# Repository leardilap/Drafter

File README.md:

# drafter

# Idea
- any usb keyboard -> transparent forward to PC as well
- [e-ink screen x3](https://www.exp-tech.de/displays/e-paper-e-ink/8887/waveshare-2.9-e-ink-raw-display-panel-three-color-296x128?c=1424)
- tinyFPGA-EX
- [ER-TFT0784-1 IPS TFT IoT LCD Display 1280x400 MIPI](https://www.buydisplay.com/7-84-inch-bar-style-ips-tft-iot-lcd-display-1280x400-mipi-for-car-monitor)
- [contition circuits to make the screen work](https://www.adafruit.com/product/4224)
- 3d printed case
- uSD card to save files -> in tinyFPGA-EX already, should be visible from the PC to copy and edit the files later on
- Firmware to print basic menu in screen and decode the keys and print in screen -> try to find a keyboard FPGA code already
- firmware also bypasses all keystrokes to connect directly to PC

## additions
- battery
- solar cell
- circuit to charge battery
- have stored in the uSD [musicforprogramming](https://musicforprogramming.net) or similar to play music tracks which help in concentration
- this requires headphone jack and sound output circuit

# Inspiration / Base
- [ultimatehackingkeyboard](https://ultimatehackingkeyboard.com)
- [Keyboard layout generator](http://www.keyboard-layout-editor.com/)
- [MrKeebs PCB generator](http://kbpcb.mrkeebs.com/)

# Phase1
- Microcontroller based keyboard
- USB-C 2.0 

# Phase2
- Bluetooth and USB-C 2.0
- Microcontroller based
- Battery
- uSD card to store info when 
# Phase3
-

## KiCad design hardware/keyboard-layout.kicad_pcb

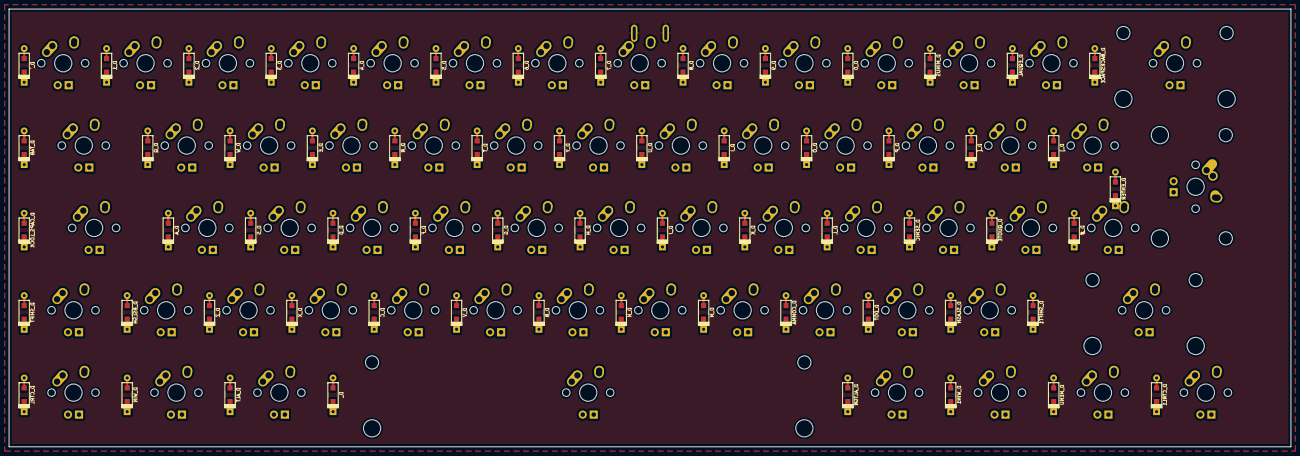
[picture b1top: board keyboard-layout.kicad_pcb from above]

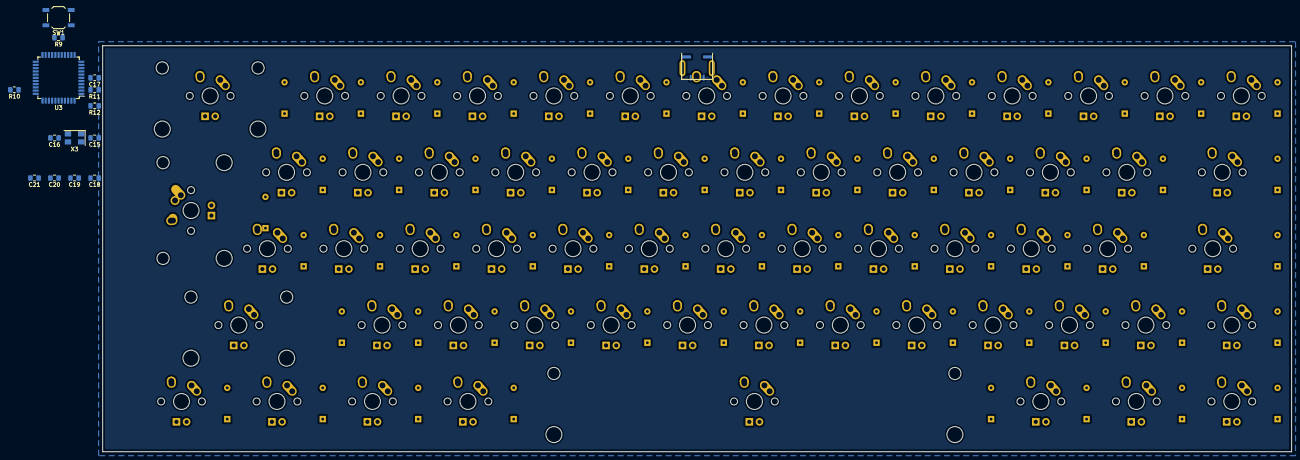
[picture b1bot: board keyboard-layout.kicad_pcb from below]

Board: 2 copper layers, 296.5 x 101.2 mm, 139 parts (15 on the bottom side), 87 nets, no tracks yet.

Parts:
C15, C16, C17, C18, C19, C20, C21: 22pF; C_0805_2012Metric_Pad1.15x1.40mm_HandSolder
D_, D_0, D_1, D_2, D_3, D_4, D_5, D_6, D_7, D_8, D_9: D; D_SOD123_axial
D_#: D; D_SOD123_axial
D_A: D; D_SOD123_axial
D_ALT: D; D_SOD123_axial
D_ALTGR: D; D_SOD123_axial
D_B: D; D_SOD123_axial
D_BACKSPACE: D; D_SOD123_axial
D_BSLSH: D; D_SOD123_axial
D_C: D; D_SOD123_axial
D_CAPS_LOCK: D; D_SOD123_axial
D_COMMA: D; D_SOD123_axial
D_CTRL, D_CTRL1: D; D_SOD123_axial
D_D: D; D_SOD123_axial
D_DOT: D; D_SOD123_axial
D_E: D; D_SOD123_axial
D_ENTER: D; D_SOD123_axial
D_EQUAL: D; D_SOD123_axial
D_F: D; D_SOD123_axial
D_G: D; D_SOD123_axial
D_H: D; D_SOD123_axial
D_I: D; D_SOD123_axial
D_J: D; D_SOD123_axial
D_K: D; D_SOD123_axial
D_L: D; D_SOD123_axial
D_M: D; D_SOD123_axial
D_MENU: D; D_SOD123_axial
D_MINUS: D; D_SOD123_axial
D_N: D; D_SOD123_axial
D_O: D; D_SOD123_axial
D_P: D; D_SOD123_axial
D_Q: D; D_SOD123_axial
D_QUOTE: D; D_SOD123_axial
D_R: D; D_SOD123_axial
D_S: D; D_SOD123_axial
D_SEMIC: D; D_SOD123_axial
D_SHIFT, D_SHIFT1: D; D_SOD123_axial
D_SLASH: D; D_SOD123_axial
D_T: D; D_SOD123_axial
D_TAB: D; D_SOD123_axial
D_U: D; D_SOD123_axial
D_V: D; D_SOD123_axial
D_W: D; D_SOD123_axial
D_WIN, D_WIN1: D; D_SOD123_axial
D_X: D; D_SOD123_axial
D_Y: D; D_SOD123_axial
D_Z: D; D_SOD123_axial
D_[: D; D_SOD123_axial
D_]: D; D_SOD123_axial
D_`: D; D_SOD123_axial
K_: KEYSW; MX-6.25U-NoLED
K_0, K_1, K_2, K_3, K_4, K_5, K_6, K_7, K_8, K_9: KEYSW; MX-1U-NoLED
K_#: KEYSW; MX-1U-NoLED
K_A: KEYSW; MX-1U-NoLED
K_ALT: KEYSW; MX-1.25U-NoLED
K_ALTGR: KEYSW; MX-1.25U-NoLED
K_B: KEYSW; MX-1U-NoLED
K_BACKSPACE: KEYSW; MX-2U-NoLED
K_BSLSH: KEYSW; MX-1U-NoLED
K_C: KEYSW; MX-1U-NoLED
K_CAPS_LOCK: KEYSW; MX-1.75U-NoLED
K_COMMA: KEYSW; MX-1U-NoLED
K_CTRL, K_CTRL1: KEYSW; MX-1.25U-NoLED
K_D: KEYSW; MX-1U-NoLED
K_DOT: KEYSW; MX-1U-NoLED
K_E: KEYSW; MX-1U-NoLED
K_ENTER: KEYSW; MX-2U-NoLED
K_EQUAL: KEYSW; MX-1U-NoLED
K_F: KEYSW; MX-1U-NoLED
K_G: KEYSW; MX-1U-NoLED
K_H: KEYSW; MX-1U-NoLED
K_I: KEYSW; MX-1U-NoLED
K_J: KEYSW; MX-1U-NoLED
K_K: KEYSW; MX-1U-NoLED
K_L: KEYSW; MX-1U-NoLED
K_M: KEYSW; MX-1U-NoLED
K_MENU: KEYSW; MX-1.25U-NoLED
K_MINUS: KEYSW; MX-1U-NoLED
K_N: KEYSW; MX-1U-NoLED
K_O: KEYSW; MX-1U-NoLED
K_P: KEYSW; MX-1U-NoLED
K_Q: KEYSW; MX-1U-NoLED
K_QUOTE: KEYSW; MX-1U-NoLED
K_R: KEYSW; MX-1U-NoLED
K_S: KEYSW; MX-1U-NoLED
K_SEMIC: KEYSW; MX-1U-NoLED
K_SHIFT: KEYSW; MX-1.25U-NoLED
K_SHIFT1: KEYSW; MX-2.75U-NoLED
K_SLASH: KEYSW; MX-1U-NoLED
K_T: KEYSW; MX-1U-NoLED
K_TAB: KEYSW; MX-1.5U-NoLED
K_U: KEYSW; MX-1U-NoLED
K_V: KEYSW; MX-1U-NoLED
K_W: KEYSW; MX-1U-NoLED
K_WIN, K_WIN1: KEYSW; MX-1.25U-NoLED
K_X: KEYSW; MX-1U-NoLED
K_Y: KEYSW; MX-1U-NoLED
K_Z: KEYSW; MX-1U-NoLED
K_[: KEYSW; MX-1U-NoLED
K_]: KEYSW; MX-1U-NoLED
K_`: KEYSW; MX-1U-NoLED
R9, R10: 10k; R_0805_2012Metric_Pad1.15x1.40mm_HandSolder
R11, R12: 22u; R_0805_2012Metric_Pad1.15x1.40mm_HandSolder
SW1: SW_PUSH; SW_SPST_TL3342
U3: ATMEGA32U4; TQFP-44_10x10mm_P0.8mm
USB3: USB_mini_micro_B; USB_miniB_hirose_5S8
X3: XTAL_GND; Crystal_SMD_5032-4Pin_5.0x3.2mm

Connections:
/col0: D_CAPS_LOCK.1, D_CTRL.1, D_SHIFT.1, D_TAB.1, D_`.1, U3.32
/col1: D_1.1, D_A.1, D_BSLSH.1, D_Q.1, D_WIN.1, U3.31
/col2: D_2.1, D_ALT.1, D_S.1, D_W.1, D_Z.1, U3.12
/col3: D_.1, D_3.1, D_D.1, D_E.1, D_X.1, U3.30
/col4: D_4.1, D_ALTGR.1, D_C.1, D_F.1, D_R.1, U3.29
/col5: D_5.1, D_G.1, D_T.1, D_V.1, D_WIN1.1, U3.28
/col6: D_6.1, D_B.1, D_H.1, D_MENU.1, D_Y.1, U3.11
/col7: D_7.1, D_CTRL1.1, D_J.1, D_N.1, D_U.1, U3.10
/col8: D_8.1, D_I.1, D_K.1, D_M.1, U3.9
/col9: D_9.1, D_COMMA.1, D_L.1, D_O.1, U3.8
/col10: D_0.1, D_DOT.1, D_P.1, D_SEMIC.1, U3.37
/col11: D_MINUS.1, D_QUOTE.1, D_SLASH.1, D_[.1, U3.38
/col12: D_#.1, D_EQUAL.1, D_SHIFT1.1, D_].1, U3.39
/col13: D_BACKSPACE.1, D_ENTER.1
GND: C15.2, C16.2, C17.2, C18.2, C19.2, C20.2, C21.2, R10.2, SW1.1, U3.5, U3.15, U3.23, USB3.5, USB3.6, X3.3
unnamed: C15.1, U3.16
unnamed: C16.1, U3.17
unnamed: C17.1, U3.6
unnamed: D_0.2, K_0.2
unnamed: D_1.2, K_1.2
unnamed: D_2.2, K_2.2
unnamed: D_3.2, K_3.2
unnamed: D_4.2, K_4.2
unnamed: D_5.2, K_5.2
unnamed: D_6.2, K_6.2
unnamed: D_7.2, K_7.2
unnamed: D_8.2, K_8.2
unnamed: D_9.2, K_9.2
unnamed: D_#.2, K_#.2
unnamed: D_.2, K_.2
unnamed: D_A.2, K_A.2
unnamed: D_ALT.2, K_ALT.2
unnamed: D_ALTGR.2, K_ALTGR.2
unnamed: D_B.2, K_B.2
unnamed: D_BACKSPACE.2, K_BACKSPACE.2
unnamed: D_BSLSH.2, K_BSLSH.2
unnamed: D_C.2, K_C.2
unnamed: D_CAPS_LOCK.2, K_CAPS_LOCK.2
unnamed: D_COMMA.2, K_COMMA.2
unnamed: D_CTRL1.2, K_CTRL1.2
unnamed: D_CTRL.2, K_CTRL.2
unnamed: D_D.2, K_D.2
unnamed: D_DOT.2, K_DOT.2
unnamed: D_E.2, K_E.2
unnamed: D_ENTER.2, K_ENTER.2
unnamed: D_EQUAL.2, K_EQUAL.2
unnamed: D_F.2, K_F.2
unnamed: D_G.2, K_G.2
unnamed: D_H.2, K_H.2
unnamed: D_I.2, K_I.2
unnamed: D_J.2, K_J.2
unnamed: D_K.2, K_K.2
unnamed: D_L.2, K_L.2
unnamed: D_M.2, K_M.2
unnamed: D_MENU.2, K_MENU.2
unnamed: D_MINUS.2, K_MINUS.2
unnamed: D_N.2, K_N.2
unnamed: D_O.2, K_O.2
unnamed: D_P.2, K_P.2
unnamed: D_Q.2, K_Q.2
unnamed: D_QUOTE.2, K_QUOTE.2
unnamed: D_R.2, K_R.2
unnamed: D_S.2, K_S.2
unnamed: D_SEMIC.2, K_SEMIC.2
unnamed: D_SHIFT1.2, K_SHIFT1.2
unnamed: D_SHIFT.2, K_SHIFT.2
unnamed: D_SLASH.2, K_SLASH.2
unnamed: D_T.2, K_T.2
unnamed: D_TAB.2, K_TAB.2
unnamed: D_U.2, K_U.2
unnamed: D_V.2, K_V.2
unnamed: D_W.2, K_W.2
unnamed: D_WIN1.2, K_WIN1.2
unnamed: D_WIN.2, K_WIN.2
unnamed: D_X.2, K_X.2
unnamed: D_Y.2, K_Y.2
unnamed: D_Z.2, K_Z.2
unnamed: D_[.2, K_[.2
unnamed: D_].2, K_].2
unnamed: D_`.2, K_`.2
unnamed: R9.1, SW1.2, U3.13
unnamed: R10.1, U3.33
unnamed: R11.1, U3.3
unnamed: R12.1, U3.4
unnamed: R11.2, USB3.2
unnamed: R12.2, USB3.3
VCC: C18.1, C19.1, C20.1, C21.1, R9.2, U3.2, U3.14, U3.24, USB3.1

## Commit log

2020-02-13 Update README.md
    remove extra bullet
2020-02-13 Update README.md
    link to screen circuits
2020-02-13 Update README.md
    headphone jack for concentration music
2020-05-05 update link
2020-05-13 init commit
2020-06-04 downloaded from mrkeebs after selecting keyboard
